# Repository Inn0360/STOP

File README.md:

**Automatic Solar Tracker - Based on Keplerian Theory**

Authors: Alice, Howin, Yuhui, Tatiana

The Automatic Solar Tracker uses the Keplerian Theory of planetary motion in order to calculate and locate the position of the sun based on its latitude and longitude. This will allow a solar panel to maximise its efficency through out the day

Features:
- Automatic longitude and latitude recognition from IP address
- Contains code to control two stepper motors for both Azimuth and Altitude Angle
- Contains files to generate 3D printed case
- Contains custom PCB for stepper motor driver chips commonly found in Arduino Kits

Applications Studio A 2020

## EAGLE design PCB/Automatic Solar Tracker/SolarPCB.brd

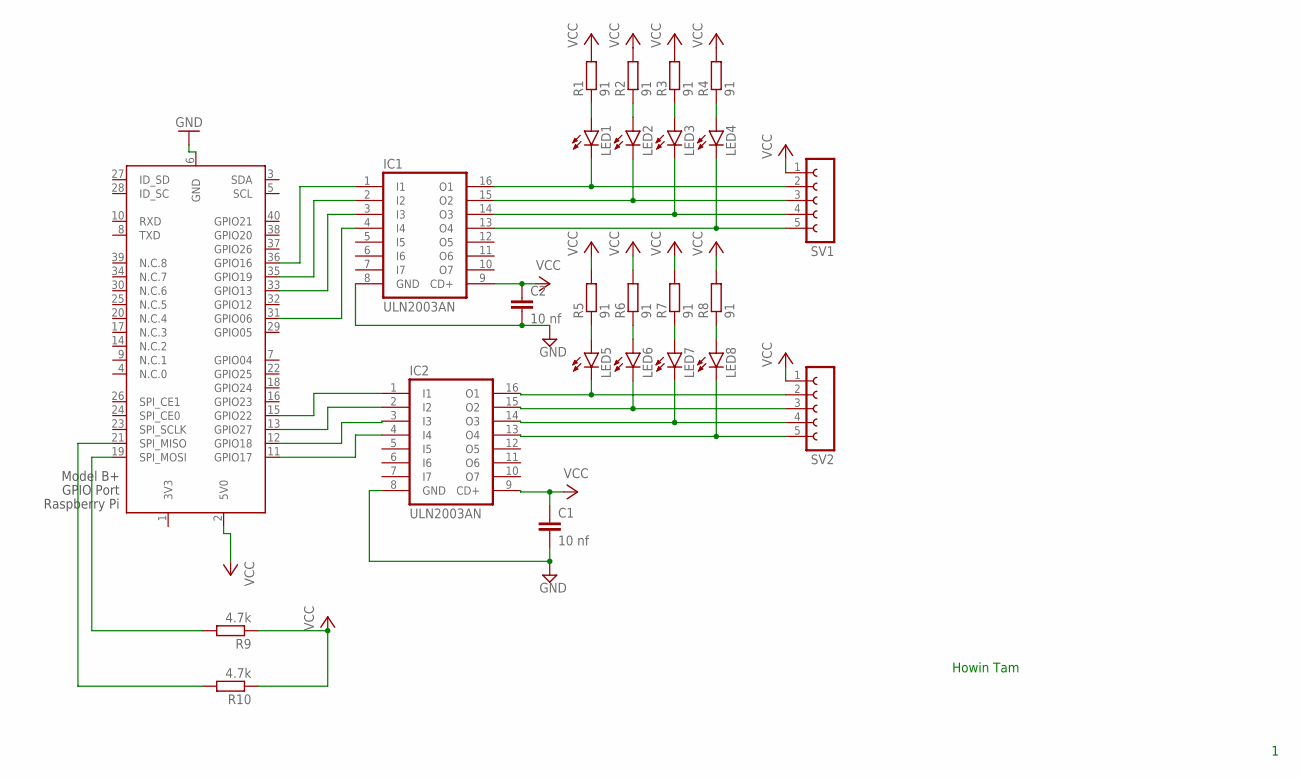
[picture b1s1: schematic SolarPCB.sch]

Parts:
C1, C2: 10 nf; C2.5-2
IC1, IC2: ULN2003AN; DIL16
LED1, LED2, LED3, LED4, LED5, LED6, LED7, LED8: LED5MM
R1, R2, R3, R4, R5, R6, R7, R8: 91; 0207/7
R9, R10: 4.7k; 0207/7
SV1, SV2: FE05-1
X1: RASPI_BOARD_B+_H; RASPI_BOARD_B+HAT

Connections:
3V3: X1.1 (3V3)
GND: C1.2, C2.2, IC1.8 (GND), IC2.8 (GND), X1.6 (GND)
unnamed: IC2.4 (I4), X1.11 (GPIO17)
unnamed: IC2.3 (I3), X1.12 (GPIO18)
unnamed: IC2.2 (I2), X1.13 (GPIO27)
unnamed: IC2.15 (O2), LED6.K (C), SV2.3
unnamed: IC2.1 (I1), X1.15 (GPIO22)
unnamed: IC1.1 (I1), X1.36 (GPIO16)
unnamed: IC1.3 (I3), X1.33 (GPIO13)
unnamed: IC1.4 (I4), X1.31 (GPIO06)
unnamed: LED1.A, R1.1
unnamed: IC1.2 (I2), X1.35 (GPIO19)
unnamed: IC2.16 (O1), LED5.K (C), SV2.2
unnamed: IC2.14 (O3), LED7.K (C), SV2.4
unnamed: IC2.13 (O4), LED8.K (C), SV2.5
unnamed: LED2.A, R2.1
unnamed: IC1.16 (O1), LED1.K (C), SV1.2
unnamed: IC1.15 (O2), LED2.K (C), SV1.3
unnamed: IC1.14 (O3), LED3.K (C), SV1.4
unnamed: IC1.13 (O4), LED4.K (C), SV1.5
unnamed: LED3.A, R3.1
unnamed: LED4.A, R4.1
unnamed: LED8.A, R8.1
unnamed: LED7.A, R7.1
unnamed: LED6.A, R6.1
unnamed: LED5.A, R5.1
unnamed: R9.2, X1.19 (SPI_MOSI)
unnamed: R10.2, X1.21 (SPI_MISO)
VCC: C1.1, C2.1, IC1.9 (CD+), IC2.9 (CD+), R1.2, R2.2, R3.2, R4.2, R5.2, R6.2, R7.2, R8.2, R9.1, R10.1, SV1.1, SV2.1, X1.2 (5V0)

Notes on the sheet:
Howin Tam

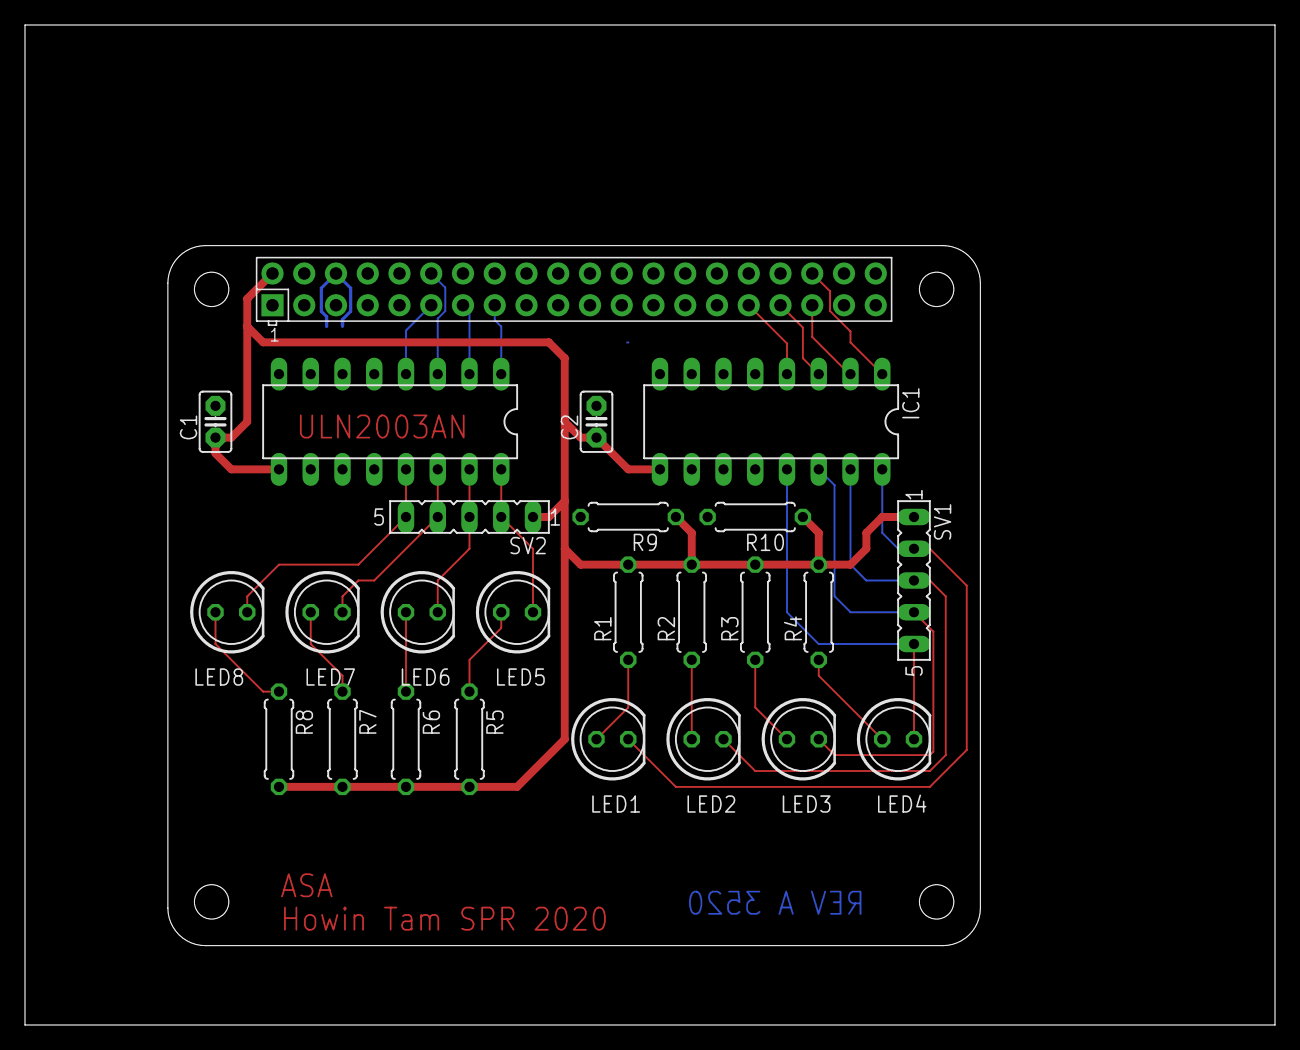
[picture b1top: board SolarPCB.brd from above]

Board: 2 copper layers, 100.0 x 80.0 mm, 25 parts (0 on the bottom side), 28 nets.

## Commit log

2020-08-16 Testing for DC Motor Control
2020-08-31 implementation of motor initialisation
2020-08-31 Addition of Yuhui's Sun_angle
2020-09-10 Trying to combine things together
2020-09-10 added local input
2020-09-11 Alice is Amazing
2020-09-12 Alice is Amazing V2
    Added Functions, and created a main function area
2020-09-21 Update to finalise first draft
    Alice and Howin both edited and worked together to reduce
2020-09-23 TESTING CONTINUES
    adventures with alice and howin -> checking to see if degree is accurate
2020-09-30 Edited MainScript
    Fixed Print Errors
2020-09-30 Added PCB Files
2020-10-20 Changes to Ensure the Motors reset properly
2020-10-30 edit bug
2020-10-31 continue bug fix
2020-11-09 Identifiy clockwise/anticlockwise issue
2020-11-10 Discovered swapped anticlockwise and clockwise for Azimuth Angle

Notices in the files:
parts and their libraries:
SparkFun-Aesthetics: Licensing: Creative Commons ShareAlike 4.0 International - https://creativecommons.org/licenses/by-sa/4.0
